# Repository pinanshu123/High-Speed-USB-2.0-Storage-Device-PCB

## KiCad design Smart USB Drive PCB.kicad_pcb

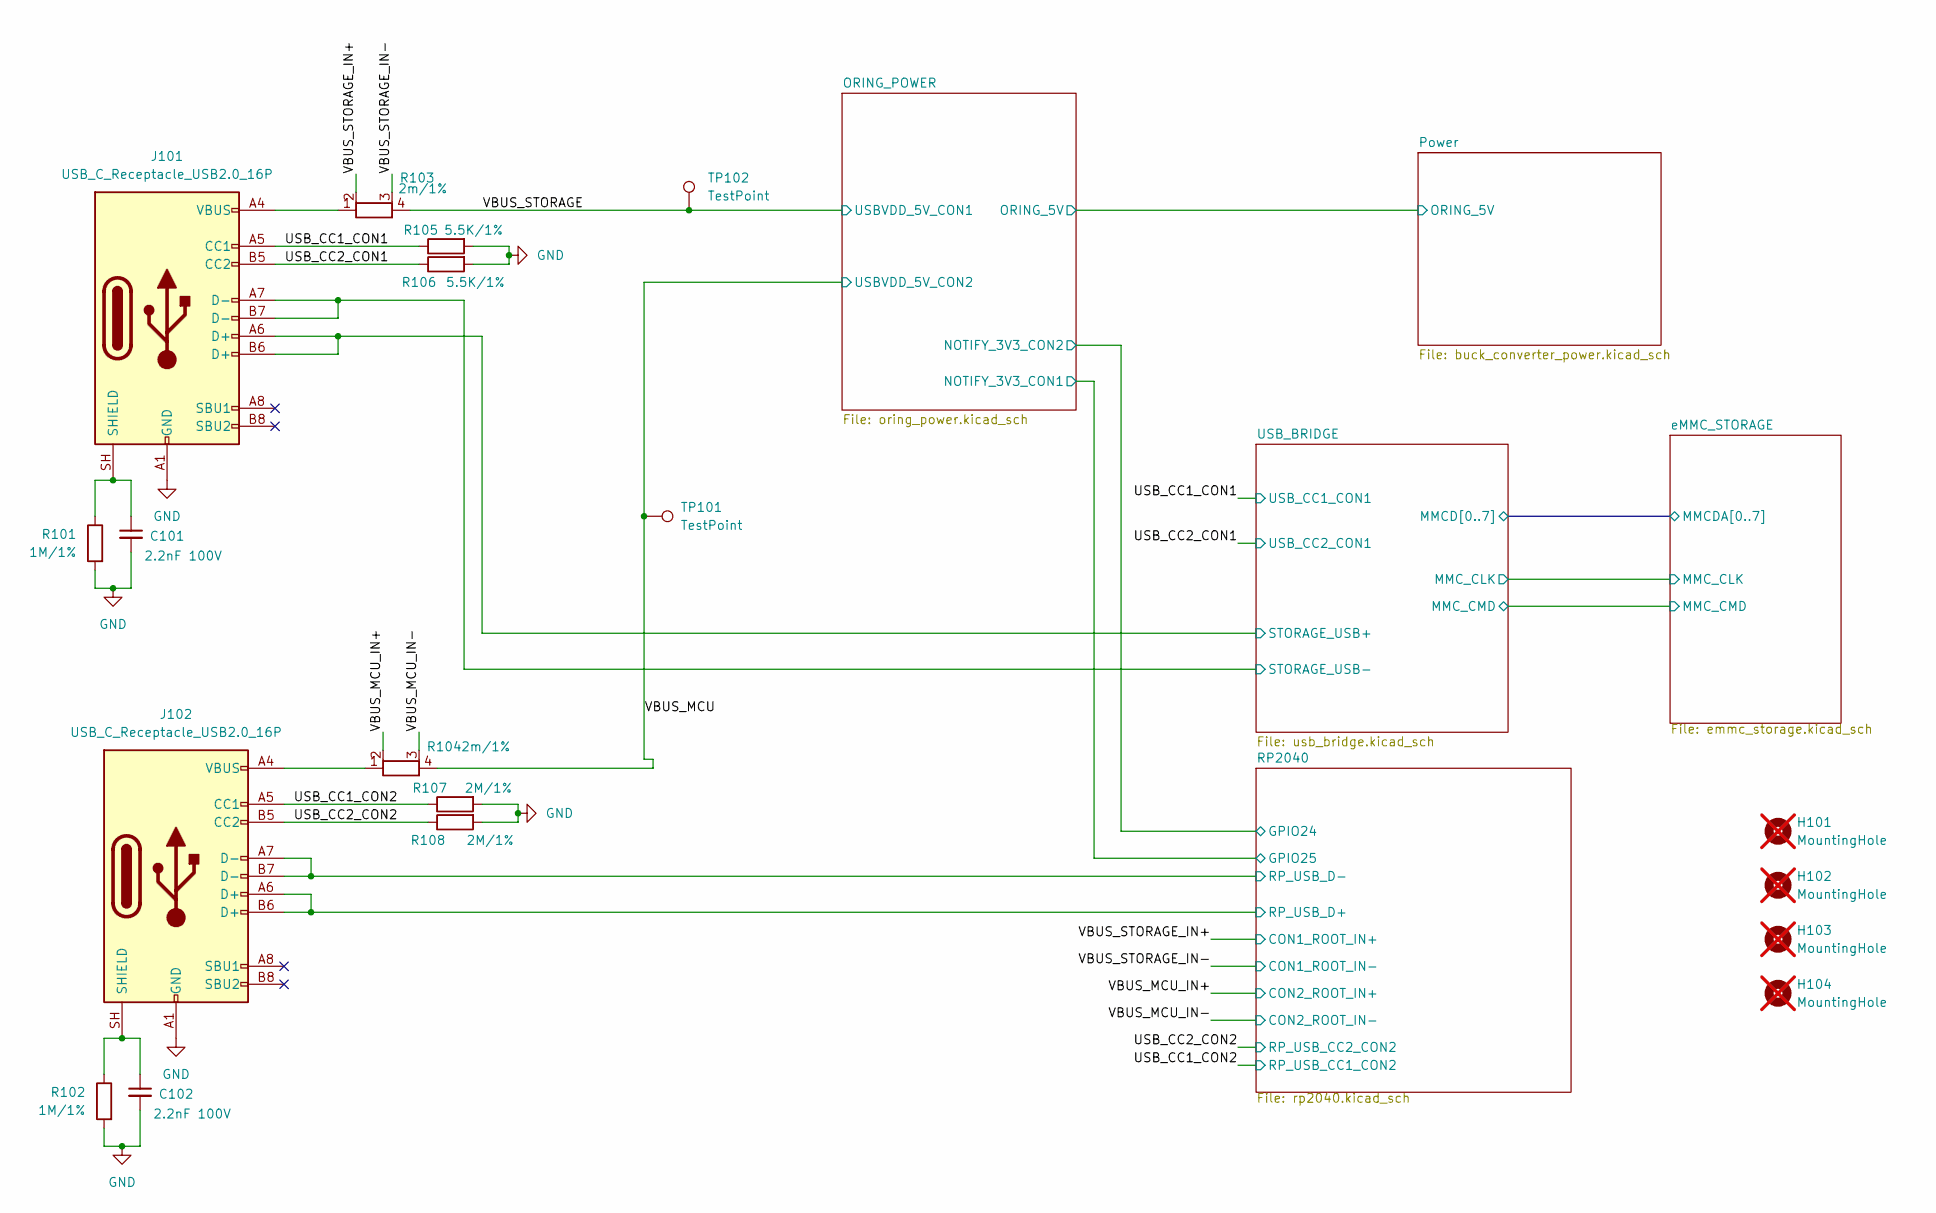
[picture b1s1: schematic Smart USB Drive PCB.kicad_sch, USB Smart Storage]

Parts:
C101, C102: 2.2nF 100V; C_0603_1608Metric
H101, H102, H103, H104: MountingHole; MountingHole_2.2mm_M2; not fitted
J101, J102: USB_C_Receptacle_USB2.0_16P; USB_C_Receptacle_XKB_U262-16XN-4BVC11
R101, R102: 1M/1%; R_01005_0402Metric
R103, R104: 2m/1%; R_Shunt_Ohmite_LVK12
R105, R106: 5.5K/1%; R_01005_0402Metric
R107, R108: 2M/1%; R_01005_0402Metric
TP101, TP102: TestPoint; TestPoint_Pad_D1.5mm

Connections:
/RP2040/RP_USB_D+: J102.A6 (D+), J102.B6 (D+); also elsewhere on the board
/RP2040/RP_USB_D-: J102.A7 (D-), J102.B7 (D-); also elsewhere on the board
/USB_BRIDGE/STORAGE_USB+: J101.A6 (D+), J101.B6 (D+); also elsewhere on the board
/USB_BRIDGE/STORAGE_USB-: J101.A7 (D-), J101.B7 (D-); also elsewhere on the board
/USB_CC1_CON1: J101.A5 (CC1), R105.1; also elsewhere on the board
/USB_CC1_CON2: J102.A5 (CC1), R107.1; also elsewhere on the board
/USB_CC2_CON1: J101.B5 (CC2), R106.1; also elsewhere on the board
/USB_CC2_CON2: J102.B5 (CC2), R108.1; also elsewhere on the board
/VBUS_MCU: R104.4, TP101.1 (1_1); also elsewhere on the board
/VBUS_MCU_IN+: R104.2; also elsewhere on the board
/VBUS_MCU_IN-: R104.3; also elsewhere on the board
/VBUS_STORAGE: R103.4, TP102.1 (1_1); also elsewhere on the board
/VBUS_STORAGE_IN+: R103.2; also elsewhere on the board
/VBUS_STORAGE_IN-: R103.3; also elsewhere on the board
GND: C101.2, C102.2, J101.A1 (GND), J101.A12 (GND), J101.B1 (GND), J101.B12 (GND), J102.A1 (GND), J102.A12 (GND), J102.B1 (GND), J102.B12 (GND), R101.2, R102.2, R105.2, R106.2, R107.2, R108.2; also elsewhere on the board
unnamed: C101.1, J101.SH (SHIELD), R101.1
unnamed: J101.A4 (VBUS), J101.A9 (VBUS), J101.B4 (VBUS), J101.B9 (VBUS), R103.1
unnamed: C102.1, J102.SH (SHIELD), R102.1
unnamed: J102.A4 (VBUS), J102.A9 (VBUS), J102.B4 (VBUS), J102.B9 (VBUS), R104.1

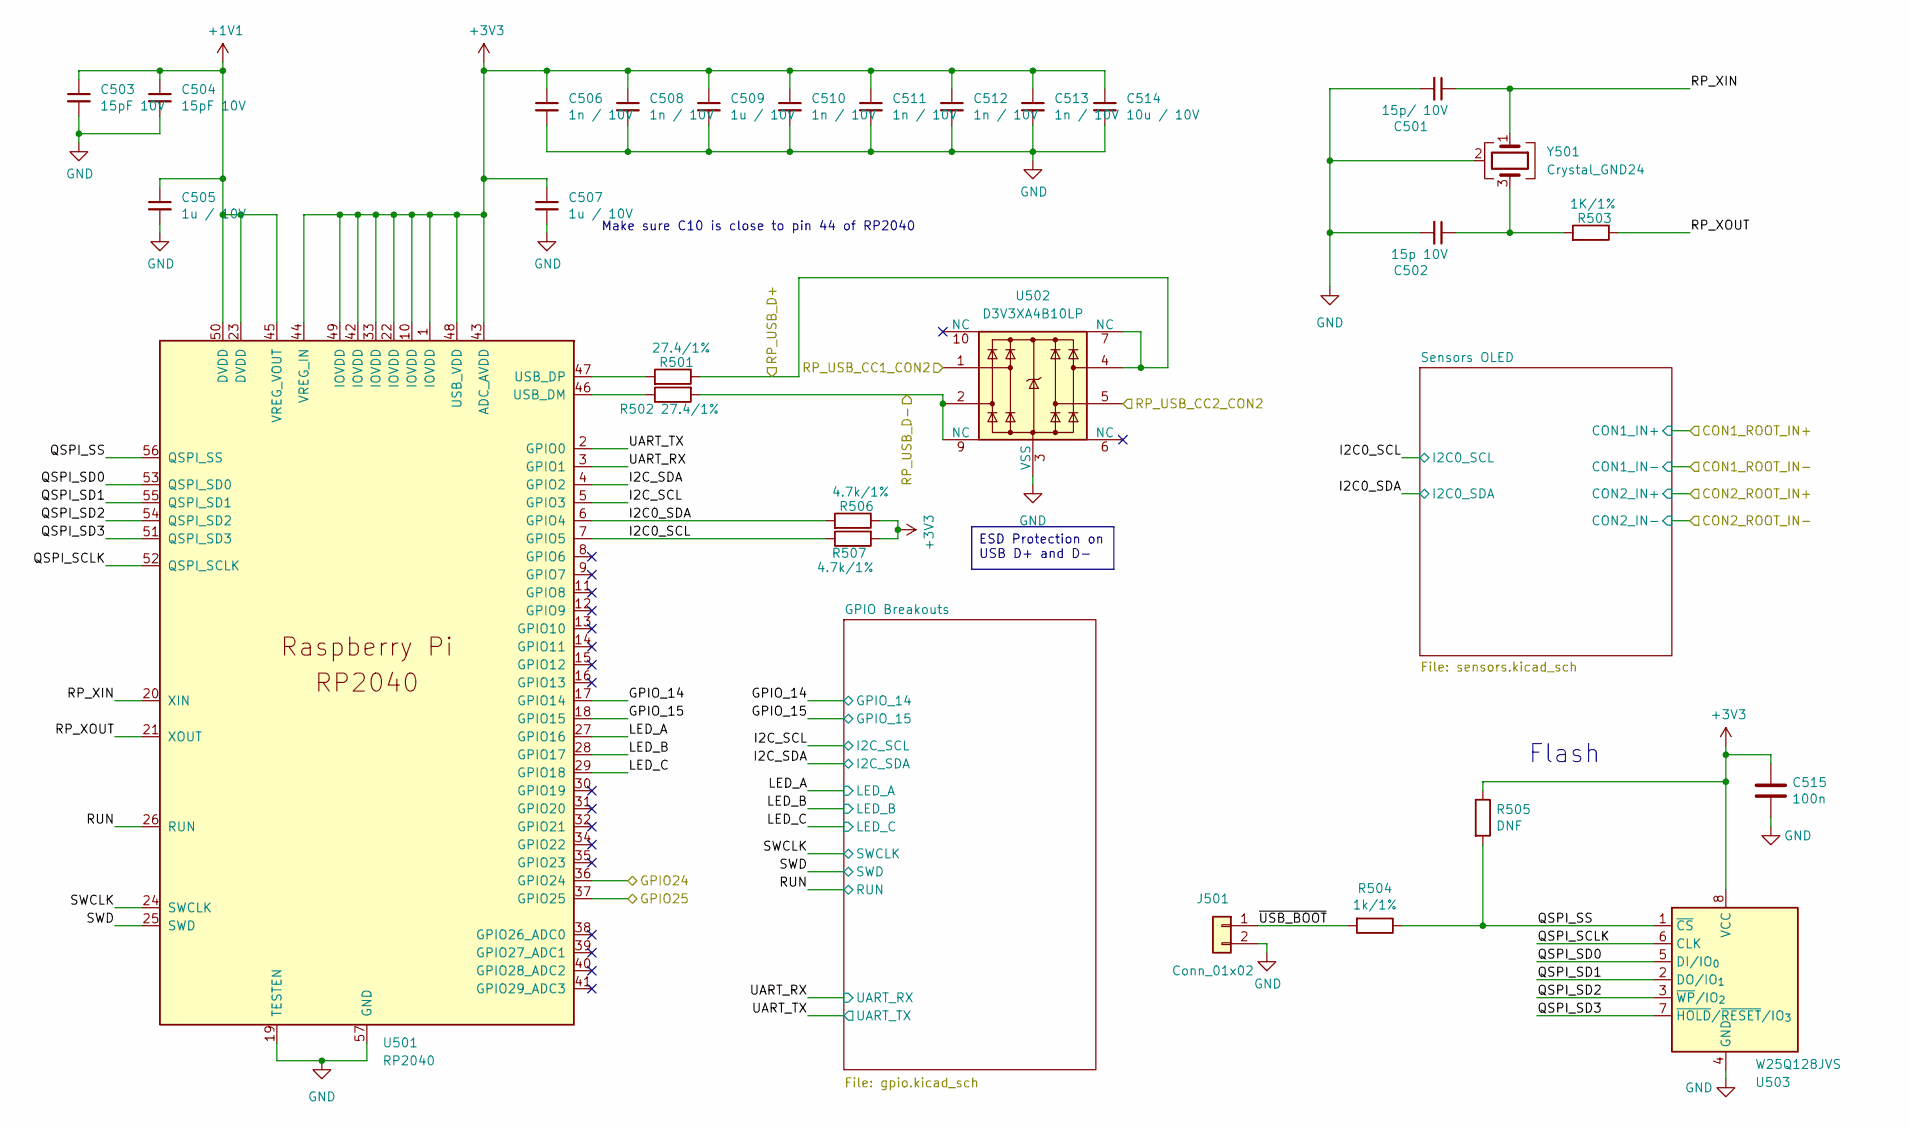
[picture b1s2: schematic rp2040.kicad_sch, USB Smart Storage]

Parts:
C501: 15p/ 10V; C_0402_1005Metric
C502: 15p 10V; C_0402_1005Metric
C503, C504: 15pF 10V; C_0402_1005Metric
C505, C507, C509: 1u / 10V; C_0402_1005Metric
C506, C508, C510, C511, C512, C513: 1n / 10V; C_0402_1005Metric
C514: 10u / 10V; C_0805_2012Metric
C515: 100n; C_0402_1005Metric
J501: Conn_01x02; PinHeader_1x02_P2.54mm_Vertical
R501, R502: 27.4/1%; R_01005_0402Metric
R503: 1K/1%; R_01005_0402Metric
R504: 1k/1%; R_0402_1005Metric
R505: DNF; R_0402_1005Metric
R506, R507: 4.7k/1%; R_01005_0402Metric
U501: RP2040; QFN-56-1EP_7x7mm_P0.4mm_EP3.2x3.2mm_ThermalVias
U502: D3V3XA4B10LP; Diodes_UDFN-10_1x2.5mm_P0.5mm
U503: W25Q128JVS; SOIC-8_5.3x5.3mm_P1.27mm
Y501: Crystal_GND24; Crystal_SMD_3225-4Pin_3.2x2.5mm

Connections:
+1V1: C503.1, C504.1, C505.1, U501.23 (DVDD), U501.45 (VREG_VOUT), U501.50 (DVDD)
+3V3: C506.1, C507.1, C508.1, C509.1, C510.1, C511.1, C512.1, C513.1, C514.1, C515.1, R505.1, R506.1, R507.2, U501.1 (IOVDD), U501.10 (IOVDD), U501.22 (IOVDD), U501.33 (IOVDD), U501.42 (IOVDD), U501.43 (ADC_AVDD), U501.44 (VREG_IN), U501.48 (USB_VDD), U501.49 (IOVDD), U503.8 (VCC); also elsewhere on the board
/ORING_POWER/NOTIFY_3V3_CON1: U501.37 (GPIO25); also elsewhere on the board
/ORING_POWER/NOTIFY_3V3_CON2: U501.36 (GPIO24); also elsewhere on the board
/RP2040/GPIO_14: U501.17 (GPIO14); also elsewhere on the board
/RP2040/GPIO_15: U501.18 (GPIO15); also elsewhere on the board
/RP2040/I2C0_SCL: R507.1, U501.7 (GPIO5); also elsewhere on the board
/RP2040/I2C0_SDA: R506.2, U501.6 (GPIO4); also elsewhere on the board
/RP2040/I2C_SCL: U501.5 (GPIO3); also elsewhere on the board
/RP2040/I2C_SDA: U501.4 (GPIO2); also elsewhere on the board
/RP2040/LED_A: U501.27 (GPIO16); also elsewhere on the board
/RP2040/LED_B: U501.28 (GPIO17); also elsewhere on the board
/RP2040/LED_C: U501.29 (GPIO18); also elsewhere on the board
/RP2040/QSPI_SCLK: U501.52 (QSPI_SCLK), U503.6 (CLK)
/RP2040/QSPI_SD0: U501.53 (QSPI_SD0), U503.5 (DI/IO_{0})
/RP2040/QSPI_SD1: U501.55 (QSPI_SD1), U503.2 (DO/IO_{1})
/RP2040/QSPI_SD2: U501.54 (QSPI_SD2), U503.3 (~WP/IO_{2})
/RP2040/QSPI_SD3: U501.51 (QSPI_SD3), U503.7 (~HOLD/~RESET/IO_{3})
/RP2040/QSPI_SS: R504.1, R505.2, U501.56 (QSPI_SS), U503.1 (~CS)
/RP2040/RP_USB_D+: R501.1, U502.4, U502.7 (NC); also elsewhere on the board
/RP2040/RP_USB_D-: R502.2, U502.2, U502.9 (NC); also elsewhere on the board
/RP2040/RP_XIN: C501.1, U501.20 (XIN), Y501.1
/RP2040/RP_XOUT: R503.1, U501.21 (XOUT)
/RP2040/RUN: U501.26 (RUN); also elsewhere on the board
/RP2040/SWCLK: U501.24 (SWCLK); also elsewhere on the board
/RP2040/SWD: U501.25 (SWD); also elsewhere on the board
/RP2040/UART_RX: U501.3 (GPIO1); also elsewhere on the board
/RP2040/UART_TX: U501.2 (GPIO0); also elsewhere on the board
/RP2040/~USB_BOOT: J501.1, R504.2
/USB_CC1_CON2: U502.1; also elsewhere on the board
/USB_CC2_CON2: U502.5; also elsewhere on the board
GND: C501.2, C502.2, C503.2, C504.2, C505.2, C506.2, C507.2, C508.2, C509.2, C510.2, C511.2, C512.2, C513.2, C514.2, C515.2, J501.2, U501.19 (TESTEN), U501.57 (GND), U502.3 (VSS), U502.8 (VSS), U503.4 (GND), Y501.2 (G), Y501.4 (G); also elsewhere on the board
unnamed: C502.1, R503.2, Y501.3
unnamed: R502.1, U501.46 (USB_DM)
unnamed: R501.2, U501.47 (USB_DP)

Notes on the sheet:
Flash
Make sure C10 is close to pin 44 of RP2040
ESD Protection on USB D+ and D-

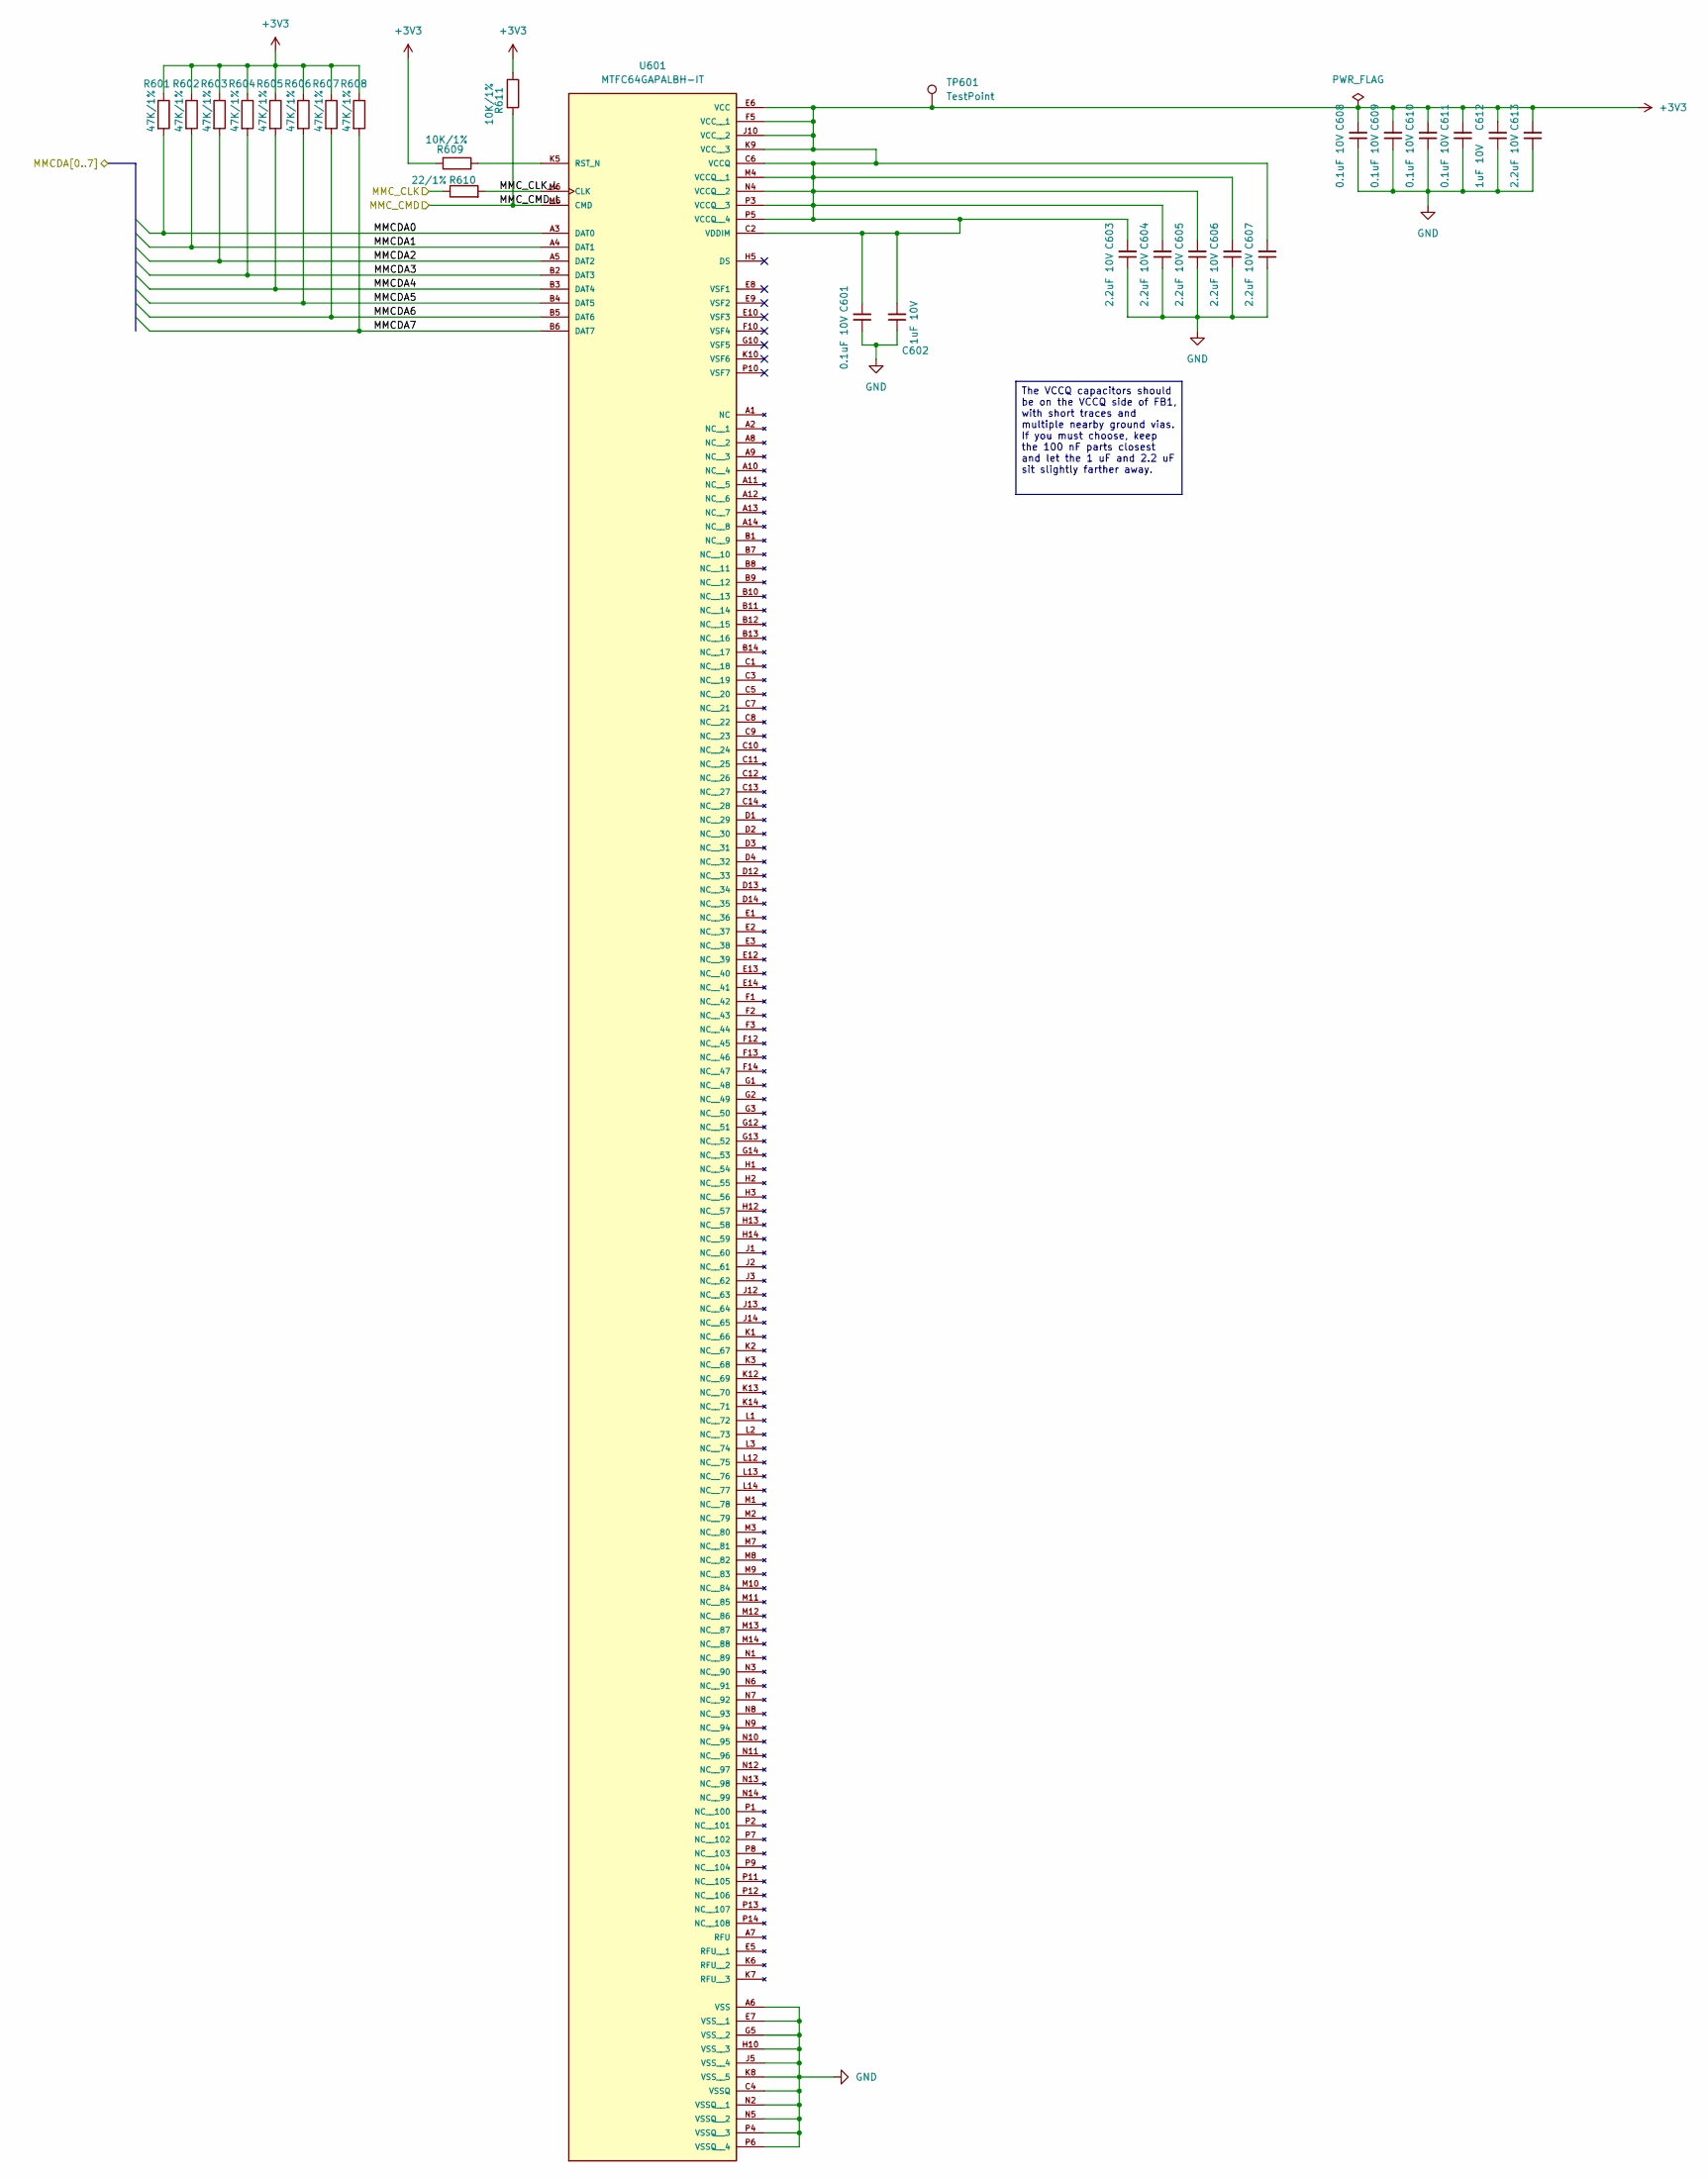
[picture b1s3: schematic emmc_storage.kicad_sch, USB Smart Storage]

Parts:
C601, C608, C609, C610, C611: 0.1uF 10V; C_0402_1005Metric
C602, C612: 1uF 10V; C_0402_1005Metric
C603, C604, C605, C606, C607, C613: 2.2uF 10V; C_0402_1005Metric
R601, R602, R603, R604, R605, R606, R607, R608: 47K/1%; R_01005_0402Metric
R609, R611: 10K/1%; R_01005_0402Metric
R610: 22/1%; R_01005_0402Metric
TP601: TestPoint; TestPoint_Pad_D1.5mm
U601: MTFC64GAPALBH-IT; BGA153N50P14X14_1300X1150X110N; PARTREV Rev. C 3/19 EN

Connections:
+3V3: C601.2, C602.2, C603.2, C604.2, C605.2, C606.2, C607.2, C608.2, C609.2, C610.2, C611.2, C612.2, C613.2, R601.1, R602.1, R603.1, R604.1, R605.1, R606.1, R607.1, R608.1, R609.2, R611.1, TP601.1 (1_1), U601.C2 (VDDIM), U601.C6 (VCCQ), U601.E6 (VCC), U601.F5 (VCC__1), U601.J10 (VCC__2), U601.K9 (VCC__3), U601.M4 (VCCQ__1), U601.N4 (VCCQ__2), U601.P3 (VCCQ__3), U601.P5 (VCCQ__4); also elsewhere on the board
/USB_BRIDGE/MMCD0: R601.2, U601.A3 (DAT0); also elsewhere on the board
/USB_BRIDGE/MMCD1: R602.2, U601.A4 (DAT1); also elsewhere on the board
/USB_BRIDGE/MMCD2: R603.2, U601.A5 (DAT2); also elsewhere on the board
/USB_BRIDGE/MMCD3: R604.2, U601.B2 (DAT3); also elsewhere on the board
/USB_BRIDGE/MMCD4: R605.2, U601.B3 (DAT4); also elsewhere on the board
/USB_BRIDGE/MMCD5: R606.2, U601.B4 (DAT5); also elsewhere on the board
/USB_BRIDGE/MMCD6: R607.2, U601.B5 (DAT6); also elsewhere on the board
/USB_BRIDGE/MMCD7: R608.2, U601.B6 (DAT7); also elsewhere on the board
/USB_BRIDGE/MMC_CLK: R610.1; also elsewhere on the board
/eMMC_STORAGE/MMC_CLK_L: R610.2, U601.M6 (CLK)
/eMMC_STORAGE/MMC_CMD_L: R611.2, U601.M5 (CMD); also elsewhere on the board
GND: C601.1, C602.1, C603.1, C604.1, C605.1, C606.1, C607.1, C608.1, C609.1, C610.1, C611.1, C612.1, C613.1, U601.A6 (VSS), U601.C4 (VSSQ), U601.E7 (VSS__1), U601.G5 (VSS__2), U601.H10 (VSS__3), U601.J5 (VSS__4), U601.K8 (VSS__5), U601.N2 (VSSQ__1), U601.N5 (VSSQ__2), U601.P4 (VSSQ__3), U601.P6 (VSSQ__4); also elsewhere on the board
unnamed: R609.1, U601.K5 (RST_N)

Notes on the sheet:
The VCCQ capacitors should be on the VCCQ side of FB1, with short traces and multiple nearby ground vias. If you must choose, keep the 100 nF parts closest and let the 1 uF and 2.2 uF sit slightly farther away.

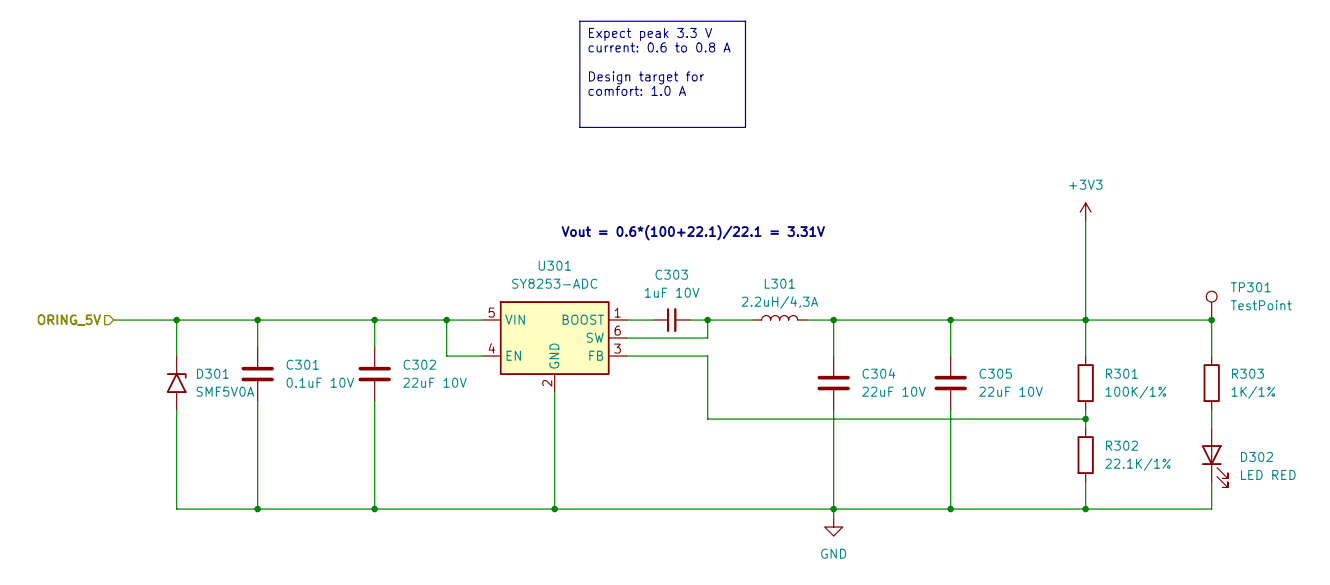
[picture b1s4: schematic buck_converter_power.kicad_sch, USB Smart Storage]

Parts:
C301: 0.1uF 10V; C_0402_1005Metric
C302: 22uF 10V; C_0805_2012Metric_Pad1.18x1.45mm_HandSolder
C303: 1uF 10V; C_0402_1005Metric
C304, C305: 22uF 10V; C_0805_2012Metric
D301: SMF5V0A; D_SMF
D302: LED RED; LED_0603_1608Metric
L301: 2.2uH/4,3A; L_Sunlord_SWPA4020S
R301: 100K/1%; R_01005_0402Metric
R302: 22.1K/1%; R_01005_0402Metric
R303: 1K/1%; R_01005_0402Metric
TP301: TestPoint; TestPoint_Pad_D1.5mm
U301: SY8253-ADC; TSOT-23-6

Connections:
+3V3: C304.1, C305.1, L301.2, R301.1, R303.1, TP301.1 (1_1); also elsewhere on the board
/ORING_POWER/ORING_5V: C301.1, C302.1, D301.1 (A1), U301.4 (EN), U301.5 (VIN); also elsewhere on the board
GND: C301.2, C302.2, C304.2, C305.2, D301.2 (A2), D302.1 (K), R302.2, U301.2 (GND); also elsewhere on the board
unnamed: D302.2 (A), R303.2
unnamed: C303.1, U301.1 (BOOST)
unnamed: R301.2, R302.1, U301.3 (FB)
unnamed: C303.2, L301.1, U301.6 (SW)

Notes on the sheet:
Vout = 0.6*(100+22.1)/22.1 = 3.31V
Expect peak 3.3 V current: 0.6 to 0.8 A Design target for comfort: 1.0 A

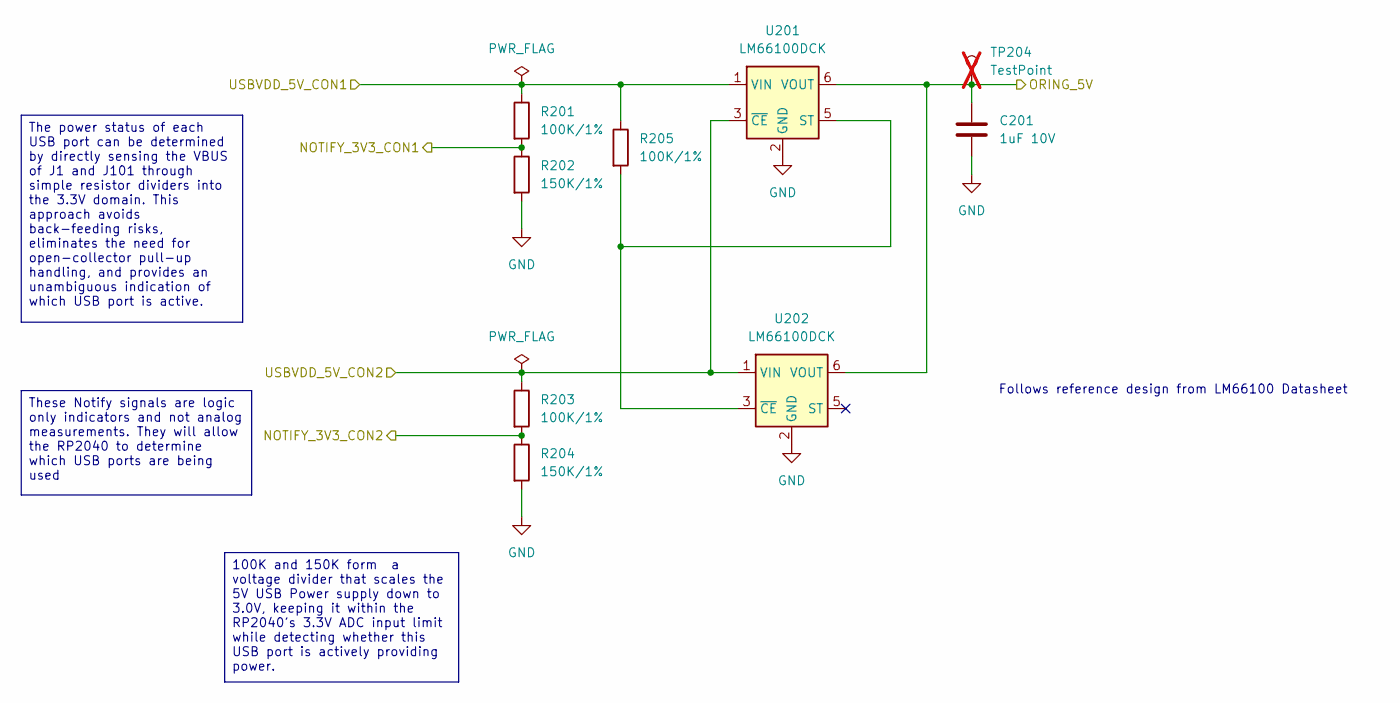
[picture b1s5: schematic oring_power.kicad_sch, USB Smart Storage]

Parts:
C201: 1uF 10V; C_0402_1005Metric
R201, R203, R205: 100K/1%; R_01005_0402Metric
R202, R204: 150K/1%; R_01005_0402Metric
TP204: TestPoint; TestPoint_Pad_D1.5mm; not fitted
U201, U202: LM66100DCK; SOT-363_SC-70-6

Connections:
/ORING_POWER/NOTIFY_3V3_CON1: R201.2, R202.1; also elsewhere on the board
/ORING_POWER/NOTIFY_3V3_CON2: R203.2, R204.1; also elsewhere on the board
/ORING_POWER/ORING_5V: C201.1, TP204.1, U201.6 (VOUT), U202.6 (VOUT); also elsewhere on the board
/VBUS_MCU: R203.1, U201.3 (~CE), U202.1 (VIN); also elsewhere on the board
/VBUS_STORAGE: R201.1, R205.1, U201.1 (VIN); also elsewhere on the board
GND: C201.2, R202.2, R204.2, U201.2 (GND), U202.2 (GND); also elsewhere on the board
unnamed: R205.2, U201.5 (ST), U202.3 (~CE)

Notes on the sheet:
Follows reference design from LM66100 Datasheet
100K and 150K form a voltage divider that scales the 5V USB Power supply down to 3.0V, keeping it within the RP2040's 3.3V ADC input limit while detecting whether this USB port is actively providing power.
These Notify signals are logic only indicators and not analog measurements. They will allow the RP2040 to determine which USB ports are being used
The power status of each USB port can be determined by directly sensing the VBUS of J1 and J101 through simple resistor dividers into the 3.3V domain. This approach avoids back-feeding risks, eliminates the need for open-collector pull-up handling, and provides an unambiguous indication of which US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

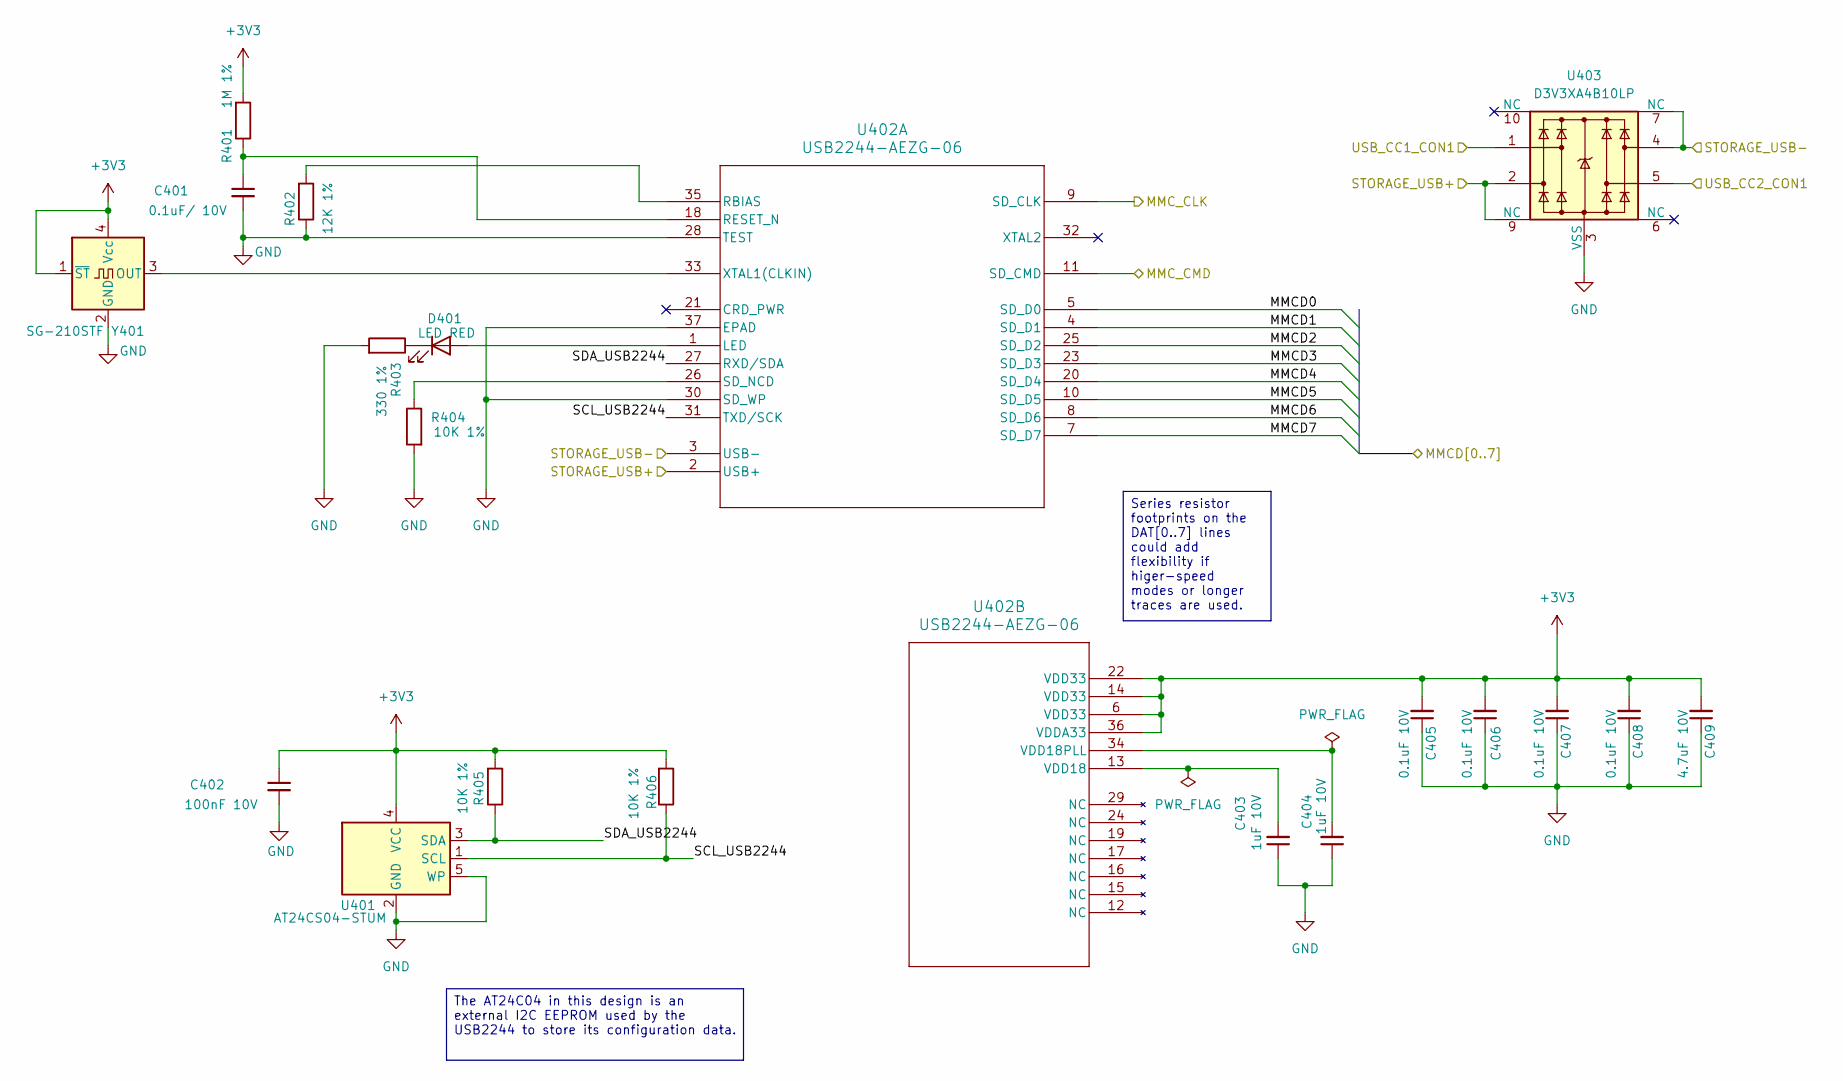
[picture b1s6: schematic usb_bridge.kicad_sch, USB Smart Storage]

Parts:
C401: 0.1uF/ 10V; C_0402_1005Metric
C402: 100nF 10V; C_0402_1005Metric
C403, C404: 1uF 10V; C_0402_1005Metric
C405, C406, C407, C408: 0.1uF 10V; C_0402_1005Metric
C409: 4.7uF 10V; C_0603_1608Metric
D401: LED RED; LED_0603_1608Metric
R401: 1M 1%; R_01005_0402Metric
R402: 12K 1%; R_01005_0402Metric
R403: 330 1%; R_01005_0402Metric
R404, R405, R406: 10K 1%; R_01005_0402Metric
U401: AT24CS04-STUM; SOT-23-5
U402: USB2244-AEZG-06; QFN36_6X6MC_MCH; digikey USB2244-AEZG-06-ND
U403: D3V3XA4B10LP; Diodes_UDFN-10_1x2.5mm_P0.5mm
Y401: SG-210STF; Oscillator_SMD_SeikoEpson_SG210-4Pin_2.5x2.0mm

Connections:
+3V3: C402.1, C405.2, C406.2, C407.2, C408.2, C409.2, R401.2, R405.2, R406.2, U401.4 (VCC), U402.6 (VDD33), U402.14 (VDD33), U402.22 (VDD33), U402.36 (VDDA33), Y401.1 (~ST), Y401.4 (Vcc); also elsewhere on the board
/USB_BRIDGE/MMCD0: U402.5 (SD_D0); also elsewhere on the board
/USB_BRIDGE/MMCD1: U402.4 (SD_D1); also elsewhere on the board
/USB_BRIDGE/MMCD2: U402.25 (SD_D2); also elsewhere on the board
/USB_BRIDGE/MMCD3: U402.23 (SD_D3); also elsewhere on the board
/USB_BRIDGE/MMCD4: U402.20 (SD_D4); also elsewhere on the board
/USB_BRIDGE/MMCD5: U402.10 (SD_D5); also elsewhere on the board
/USB_BRIDGE/MMCD6: U402.8 (SD_D6); also elsewhere on the board
/USB_BRIDGE/MMCD7: U402.7 (SD_D7); also elsewhere on the board
/USB_BRIDGE/MMC_CLK: U402.9 (SD_CLK); also elsewhere on the board
/USB_BRIDGE/SCL_USB2244: R406.1, U401.1 (SCL), U402.31 (TXD/SCK)
/USB_BRIDGE/SDA_USB2244: R405.1, U401.3 (SDA), U402.27 (RXD/SDA)
/USB_BRIDGE/STORAGE_USB+: U402.2 (USB+), U403.2, U403.9 (NC); also elsewhere on the board
/USB_BRIDGE/STORAGE_USB-: U402.3 (USB-), U403.4, U403.7 (NC); also elsewhere on the board
/USB_CC1_CON1: U403.1; also elsewhere on the board
/USB_CC2_CON1: U403.5; also elsewhere on the board
/eMMC_STORAGE/MMC_CMD_L: U402.11 (SD_CMD); also elsewhere on the board
GND: C401.2, C402.2, C403.1, C404.1, C405.1, C406.1, C407.1, C408.1, C409.1, R402.1, R403.2, R404.2, U401.2 (GND), U401.5 (WP), U402.28 (TEST), U402.30 (SD_WP), U402.37 (EPAD), U403.3 (VSS), U403.8 (VSS), Y401.2 (GND); also elsewhere on the board
unnamed: D401.2 (A), U402.1 (LED)
unnamed: D401.1 (K), R403.1
unnamed: R402.2, U402.35 (RBIAS)
unnamed: C401.1, R401.1, U402.18 (RESET_N)
unnamed: R404.1, U402.26 (SD_NCD)
unnamed: U402.33 (XTAL1(CLKIN)), Y401.3 (OUT)
unnamed: C403.2, U402.13 (VDD18)
unnamed: C404.2, U402.34 (VDD18PLL)

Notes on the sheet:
The AT24C04 in this design is an external I2C EEPROM used by the USB2244 to store its configuration data.
Series resistor footprints on the DAT[0..7] lines could add flexibility if higer-speed modes or longer traces are used.

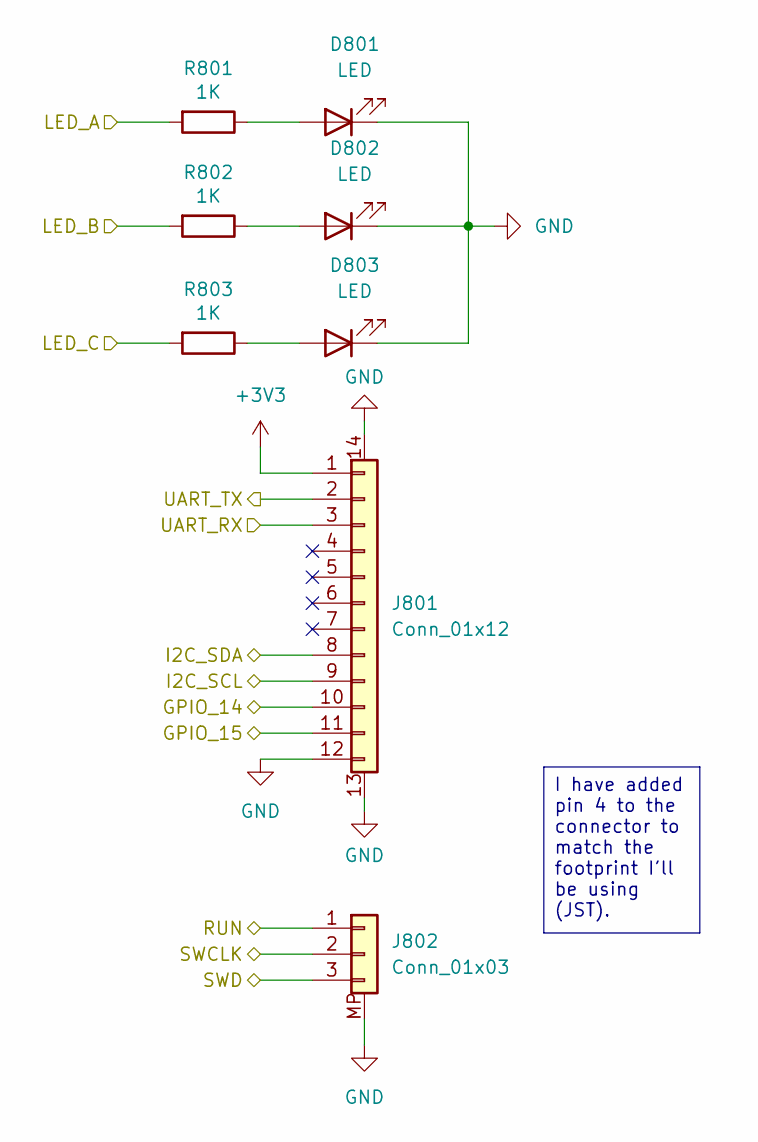
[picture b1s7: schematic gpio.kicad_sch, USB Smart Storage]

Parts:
D801, D802, D803: LED; LED_0603_1608Metric
J801: Conn_01x12; JST_SH_SM12B-SRSS-TB_1x12-1MP_P1.00mm_Horizontal
J802: Conn_01x03; JST_GH_SM03B-GHS-TB_1x03-1MP_P1.25mm_Horizontal
R801, R802, R803: 1K; R_0402_1005Metric

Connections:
+3V3: J801.1; also elsewhere on the board
/RP2040/GPIO_14: J801.10; also elsewhere on the board
/RP2040/GPIO_15: J801.11; also elsewhere on the board
/RP2040/I2C_SCL: J801.9; also elsewhere on the board
/RP2040/I2C_SDA: J801.8; also elsewhere on the board
/RP2040/LED_A: R801.2; also elsewhere on the board
/RP2040/LED_B: R802.2; also elsewhere on the board
/RP2040/LED_C: R803.2; also elsewhere on the board
/RP2040/RUN: J802.1; also elsewhere on the board
/RP2040/SWCLK: J802.2; also elsewhere on the board
/RP2040/SWD: J802.3; also elsewhere on the board
/RP2040/UART_RX: J801.3; also elsewhere on the board
/RP2040/UART_TX: J801.2; also elsewhere on the board
GND: D801.1 (K), D802.1 (K), D803.1 (K), J801.12, J801.13 (MP1), J801.14 (MP2), J802.MP; also elsewhere on the board
unnamed: D801.2 (A), R801.1
unnamed: D802.2 (A), R802.1
unnamed: D803.2 (A), R803.1

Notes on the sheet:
I have added pin 4 to the connector to match the footprint I'll be using (JST).
